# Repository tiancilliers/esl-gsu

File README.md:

This repository contains the design files for the satellite interfacing module in development by the ESL. More information will follow soon.

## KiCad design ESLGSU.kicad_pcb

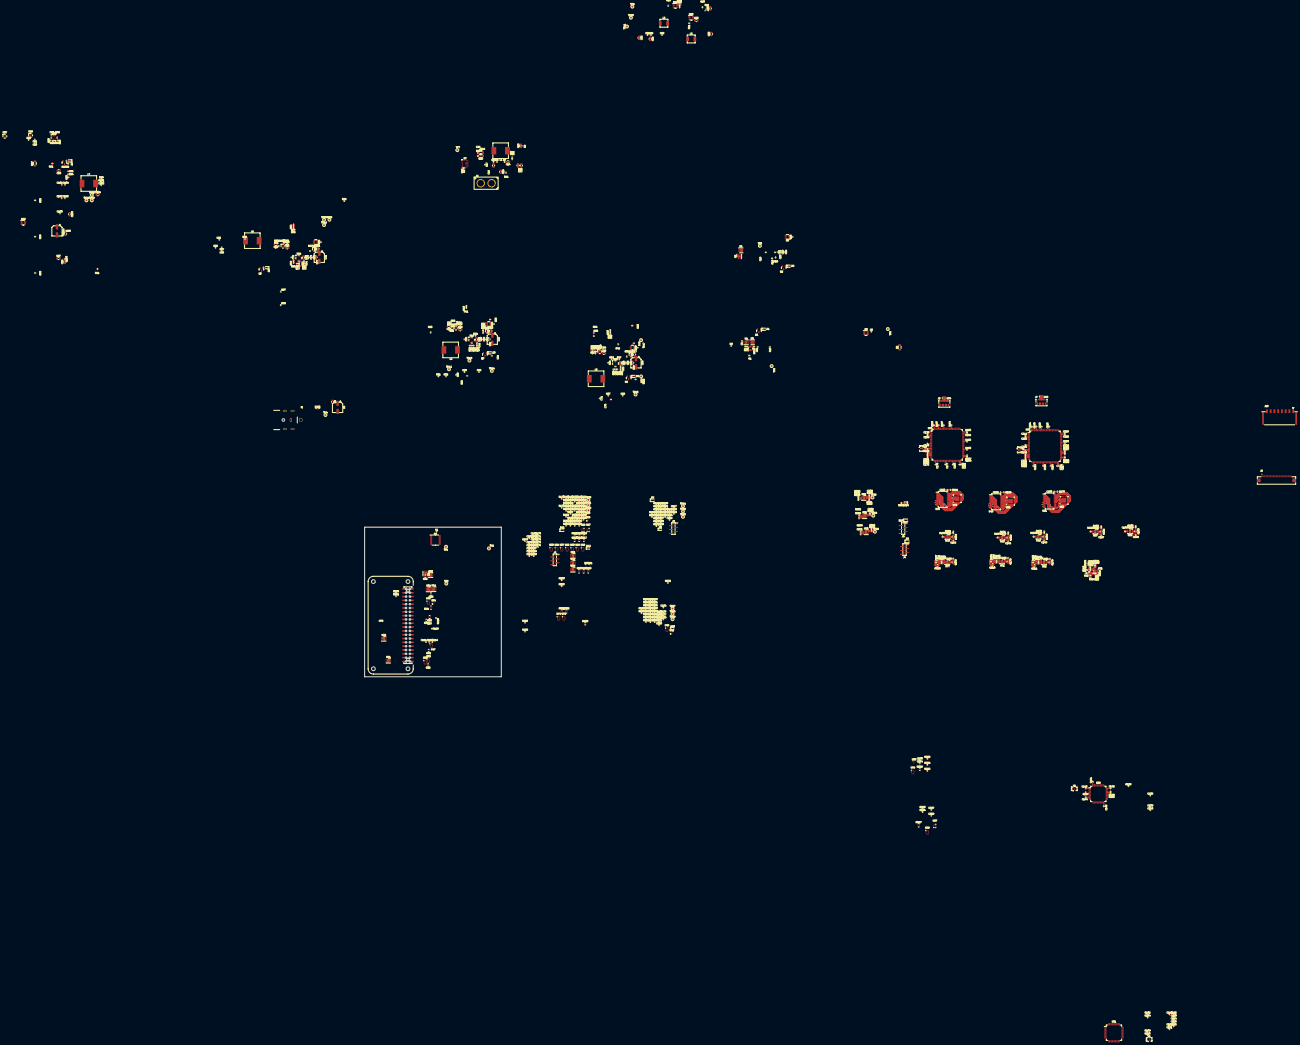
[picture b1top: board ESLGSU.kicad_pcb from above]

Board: 6 copper layers, 698 parts (0 on the bottom side), 467 nets.

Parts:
C1, C3, C5, C11, C12, C13, C17, C21, C25, C27, C31, C32, C36, C37, C38, C39, C48, C54, C55, C56, C57, C66, C72, C73, C74, C75, C84, C90, C91, C92, C93, C102, C108, C109, C110, C111, C112, C113, C114, C117, C118, C119, C122, C123, C124, C125, C126, C127, C128, C129, C130, C131, C132, C133, C136, C137, C138, C141, C142, C143, C144, C145, C146, C147, C148, C149, C150, C151, C152, C153, C154, C155, C156, C157, C158, C161, C162, C163, C164, C165, C166, C167, C168, C169, C170, C171, C172, C173, C174, C176, C177, C180, C181, C182, C183, C184, C187, C188, C189, C190, C191, C192, C193, C194, C195, C196, C197, C198, C199, C200, C201, C203, C204, C205, C206, C207, C208, C209, C210, C212, C213, C216, C217, C218, C219, C220, C223, C224, C225, C226, C227, C228, C229, C230: 100n; C_0402_1005Metric
C2, C16, C49, C52, C53, C67, C70, C71, C85, C88, C89, C103, C106, C107, C121, C140, C175, C179, C211, C215: 1u; C_0402_1005Metric
C4, C20, C42, C60, C78, C96: 22n; C_0402_1005Metric
C6, C7, C8, C18, C19, C30, C35: 10u; C_0805_2012Metric
C9, C40, C58, C76, C94: 100u; CP_Elec_6.3x7.7
C10, C24: 1n; C_0402_1005Metric
C14, C15, C22, C23, C28, C29, C33, C34, C41, C43, C44, C45, C46, C47, C59, C61, C62, C63, C64, C65, C77, C79, C80, C81, C82, C83, C95, C97, C98, C99, C100, C101: 22u; C_0805_2012Metric
C26, C120, C139, C178, C214: 4.7u; C_0402_1005Metric
C50, C68, C86, C104: 220p; C_0402_1005Metric
C51, C69, C87, C105: 2.2n; C_0402_1005Metric
C115, C134, C159, C160, C202: 100p; C_0402_1005Metric
C116, C135, C185, C186, C221, C222: 2.2u; C_0402_1005Metric
D1, D2, D3, D4, D5, D6, D8, D10, D12, D14: TZ-P2-0603GTCS1-0.6T; LED_0603_1608Metric
D7, D9, D11, D13: 1N5819; D_SOD-323
J1: PJ-080BH; PJ-082BH
J2: XT60U-M; XT60
J3, J4, J6, J8: Conn_01x06_Pin; PinHeader_1x06_P1.27mm_Vertical_SMD_Pin1Right
J5, J7: 10118194-0001LF; AMPHENOL_10118194-0001LF
J9: AMPHENOL_62684-401100ALF
J10: 1054301108; MOLEX_1054301108
L1, L4, L5, L6, L7: SRP1038A-4R7M; L_Vishay_IHLP-4040
L2, L3: SPM5020T-4R7M-LR; L_Vishay_IHLP-2020
Q1, Q2, Q3, Q4, Q5, Q6: RE1C002UNTCL; SOT-23
R1, R13: 200R; R_0402_1005Metric
R2, R14, R15, R16, R17, R119, R120, R122, R123, R152, R153, R155, R156, R176, R177, R190, R191, R192, R193, R194, R195, R196, R197, R230, R231, R237, R245, R246, R247, R248, R267, R268: 10K; R_0402_1005Metric
R3, R18: 20K; R_0402_1005Metric
R4, R9, R10, R31, R49, R72, R87: 5m; R_1206_3216Metric
R5, R6, R24, R25, R42, R43, R66, R67, R81, R82, R104, R109, R110, R111, R113, R121, R125, R133, R134, R137, R142, R143, R144, R146, R154, R158, R166, R167, R198, R204, R207, R213, R214, R222, R224, R227, R229, R249, R253, R255, R260, R261, R265, R270: 0R; R_0402_1005Metric
R7, R8, R11, R12: 1R; R_0402_1005Metric
R19, R21, R47, R105, R114, R127, R138, R147, R160, R170, R171, R172, R182, R184, R202, R203, R217, R218, R233, R234, R240, R252, R263: 100K; R_0402_1005Metric
R20, R22: 5.6K; R_0402_1005Metric
R23, R36, R54, R76, R91: 27K; R_0402_1005Metric
R26, R44, R68, R83: 47K; R_0402_1005Metric
R27, R45, R69, R84, R130, R163, R201, R251: 33R; R_0402_1005Metric
R28, R33, R46, R51, R52, R70, R74, R85, R89, R102, R106, R107, R108, R115, R116, R117, R118, R126, R128, R129, R131, R135, R139, R140, R141, R148, R149, R150, R151, R159, R161, R162, R164, R173, R174, R175, R180, R181, R183, R185, R186, R187, R188, R189, R199, R200, R205, R206, R208, R209, R210, R211, R215, R216, R219, R220, R221, R225, R226, R235, R236, R239, R241, R242, R243, R244, R250, R254, R256, R257, R258, R262, R264, R269, R272, R273: 200K; R_0402_1005Metric
R29, R37, R55, R56, R77, R92: 15K; R_0402_1005Metric
R30, R40, R58, R79, R94: 22K; R_0402_1005Metric
R32, R50, R73, R88: 8.2K; R_0402_1005Metric
R34: 330K; R_0402_1005Metric
R35: 1.5K; R_0402_1005Metric
R38: 12K; R_0402_1005Metric
R39, R71, R86: 150K; R_0402_1005Metric
R41, R59, R80, R95: 1K; R_0402_1005Metric
R48, R78, R93: 51K; R_0402_1005Metric
R53: 2.2K; R_0402_1005Metric
R57: 75K; R_0402_1005Metric
R60, R61, R62, R63, R64, R65, R96, R97, R98, R99, R100, R101: 4.7K; R_0402_1005Metric
R75, R90: 220K; R_0402_1005Metric
R103, R136, R168, R169, R178, R179, R232, R238: 120R; R_0805_2012Metric
R112, R124, R132, R145, R157, R165, R212, R223, R228, R259, R266, R271: 510R; R_0402_1005Metric
RN1, RN2, RN5, RN10, RN11, RN12, RN14, RN16, RN17, RN20, RN23, RN24, RN26: 0R; R_Array_Convex_2x0402
RN3, RN6, RN13, RN15, RN25: 10K; R_Array_Convex_2x0402
RN4, RN7, RN8, RN9, RN18, RN19, RN21, RN22, RN27: 0R; R_Array_Concave_4x0402
TP1, TP2, TP3, TP4, TP5, TP6, TP7, TP8, TP9, TP10, TP11, TP12, TP13, TP14, TP15, TP16, TP17, TP18, TP19, TP20, TP21, TP22, TP23, TP24, TP25, TP26, TP27, TP28, TP29, TP30, TP31, TP32, TP33, TP34, TP35: TestPoint; TestPoint_Pad_D1.5mm
U1: TCA9544APWR; TSSOP-20_4.4x6.5mm_P0.65mm
U2, U6: VBQF1303; V-DFN3030-8
U3, U13, U17, U21, U25: INA219AIDCNR; SOT-23-8
U4, U8: NCP45770IMN24TWG; WDFN-12-1EP_3x3mm_P0.45mm_EP1.7x2.5mm
U5, U9: AP74700QW6-7; SOT-23-6
U7: MP2651GVT; TQFN30_MP2651
U10: AP63205WU-7; TSOT-23-6
U11: TPS2121RUXR; Texas_VQFN-HR-12_2x2.5mm_P0.5mm_ThermalVias
U12: AP63203WU-7; TSOT-23-6
U14, U18, U22, U26: LM73100RPWR; VQFN-HR
U15, U19, U23, U27: TPS259474LRPWR; VQFN-HR
U16, U20, U24, U28: MP28167-A; QFN-16-MP28167
U29, U37, U45, U46, U73: TCAN1051GVDRBRQ; DFN-8-1EP_3x3mm_P0.65mm_EP1.55x2.4mm
U30, U33, U36, U38, U41, U44, U65, U70, U71, U86, U89, U90: TPS2115ADRBR; VSON-8-1EP_3x3mm_P0.65mm_EP1.65x2.4mm_ThermalVias
U31, U39: STM32F412RETx; LQFP-64_10x10mm_P0.5mm
U32, U35, U40, U43, U47, U53, U56, U57, U62, U63, U68, U69, U74, U78, U81, U84, U88: TMUX1574RSVR; T-UQFN-16
U34, U42, U58, U59, U82: FXMA2102L8X; UQFN8_MICROPAK
U48, U75, U91: CY8C9520A; SSOP-28_5.3x10.2mm_P0.65mm
U49, U50, U60, U61, U76, U83: TXU0202DTTR; SOT833-1-XSON8
U51, U52, U77: THVD1450DRBR; DFN-8-1EP_3x3mm_P0.65mm_EP1.55x2.4mm
U54, U80: ESD7004MUTAG; UDFN10_ESD
U55, U79, U92: PCAL6524HEAZ; HVQFN-32-1EP_5x5mm_P0.5mm_EP3.1x3.1mm
U64, U85: STM32H743ZITx; LQFP-144_20x20mm_P0.5mm
U66, U67, U87: TXB0104RUT; T-UQFN-12
U72: FH-00339; PI_ZERO_2_W
Y1, Y2, Y3, Y4: CSTNE8M00G55A; Resonator_SMD_Murata_CSTxExxV-3Pin_3.0x1.1mm

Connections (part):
/BUS_3V3: C110.2, C129.2, C169.2, J10.1, R31.2, R113.2, R146.2, R224.2, TP14.1, U13.2 (IN-), U30.8 (IN1), U38.8 (IN1), U70.8 (IN1)
/BUS_5V: C112.2, C131.2, C173.2, J10.2, R49.1, R125.2, R158.2, R229.2, TP17.1, U17.2 (IN-), U33.8 (IN1), U41.8 (IN1), U71.8 (IN1)
/BUS_CH1: J10.7, R72.1, TP20.1, U21.2 (IN-)
/BUS_CH2: J10.8, R87.1, TP23.1, U25.2 (IN-)
/BUS_UNREG: C49.1, C67.1, C85.1, C103.1, J10.4, J10.5, R4.2, R28.1, R46.1, R70.1, R85.1, TP6.1, U3.2 (IN-), U15.5 (IN), U19.5 (IN), U23.5 (IN), U27.5 (IN)
/CAN1_H: J9.03 (Pin_3), R103.1, R136.1, R168.1, R232.1, U29.7 (CANH), U37.7 (CANH), U45.7 (CANH), U73.7 (CANH)
/CAN1_L: J9.02 (Pin_2), R103.2, R136.2, R168.2, R232.2, U29.6 (CANL), U37.6 (CANL), U45.6 (CANL), U73.6 (CANL)
/CAN2_H: J9.05 (Pin_5), R169.1, U46.7 (CANH)
/CAN2_L: J9.04 (Pin_4), R169.2, U46.6 (CANL)
/CFGI2C_SCL: R231.2, RN20.1 (R1.1), U48.10 (SCL), U55.26 (ADDR), U55.29 (SCL), U72.5 (GPIO3_SCL), U75.10 (SCL), U79.29 (SCL), U91.10 (SCL), U92.29 (SCL)
/CFGI2C_SDA: R230.2, RN20.2 (R2.1), U48.11 (SDA), U55.30 (SDA), U72.3 (GPIO2_SDA), U75.11 (SDA), U79.26 (ADDR), U79.30 (SDA), U91.11 (SDA), U92.30 (SDA)
/EPS_I2C_INT: TP3.1, U1.17 (~INT), U85.80 (PD11)
/EPS_I2C_SCL: R267.2, RN20.4 (R1.2), TP1.1, U1.18 (SCL), U3.5 (SCL), U7.4 (SCL), U85.81 (PD12)
/EPS_I2C_SDA: R268.2, RN20.3 (R2.2), TP2.1, U1.19 (SDA), U3.6 (SDA), U7.3 (SDA), U85.82 (PD13)
/EPS_uC/BOOTLDR: R243.2, U72.40 (GPIO21), U85.138 (BOOT0)
/EPS_uC/CAN1_RX: U73.4 (RXD), U85.139 (PB8)
/EPS_uC/CAN1_SE: R234.1, R236.2, U73.8 (S), U75.1 (P0_0), U79.1 (P0_0)
/EPS_uC/CAN1_TX: U73.1 (TXD), U85.140 (PB9)
/EPS_uC/GPIO_nEN: R233.1, R235.2, U74.13 (nEN), U75.12 (P2_3_A1), U78.13 (nEN), U79.20 (P2_3)
/EPS_uC/I2C1_EN: R250.1, U75.3 (P0_2), U79.3 (P0_2), U82.5 (OE)
/EPS_uC/I2C1_nPEN: R240.1, R241.1, U75.4 (P0_3), U79.4 (P0_3), U81.13 (nEN)
/EPS_uC/LED: R251.1, U85.34 (PA0)
/EPS_uC/PISPI_NSS: U72.35 (GPIO19), U85.40 (PA4)
/EPS_uC/RS4851_EN: R237.2, R239.1, U75.2 (P0_1), U77.2 (nRE), U77.3 (DE), U79.2 (P0_1)
/EPS_uC/RS4851_RX: RN23.4 (R1.2), U76.4 (A2Y), U85.114 (PD0)
/EPS_uC/RS4851_TX: RN23.3 (R2.2), U76.5 (A1), U85.115 (PD1)
/EPS_uC/RS4851_TXE: R237.1, U85.118 (PD4)
/EPS_uC/SPI1_nEN: R263.1, R264.2, U75.7 (P0_6), U79.7 (P0_6), U88.13 (nEN)
/EPS_uC/SPI_SHIFT: U75.8 (P0_7), U79.8 (P0_7), U87.12 (OE), U88.15 (SEL)
/EPS_uC/SUB3V3: C194.2, C197.2, C203.2, C209.2, C211.1, C212.1, C213.1, C214.1, C215.1, C216.1, C217.1, C218.1, C219.1, C220.1, C223.1, C224.1, C225.1, C226.1, C227.1, C228.1, C229.1, D13.1 (K), R245.1, R246.1, R265.1, R267.1, R268.1, TP34.1, U73.5 (VIO), U76.3 (VCCA), U76.6 (OE), U82.1 (VREF1), U83.3 (VCCA), U83.6 (OE), U85.6 (VBAT), U85.17 (VDD), U85.30 (VDD), U85.32 (VREF+), U85.33 (VDDA), U85.39 (VDD), U85.52 (VDD), U85.62 (VDD), U85.72 (VDD), U85.84 (VDD), U85.95 (VDD33_USB), U85.108 (VDD), U85.121 (VDD), U85.131 (VDD), U85.144 (VDD), U87.1 (VCCA), U89.7 (OUT)
/EPS_uC/SUB5V: C195.2, R234.2, R270.1, TP35.1, U73.3 (VCC), U90.7 (OUT)
/EPS_uC/SWCLK: J8.4, U85.109 (PA14)
/EPS_uC/SWDIO: J8.3, U85.105 (PA13)
/EPS_uC/SWO: J8.5, U85.133 (PB3)
/EPS_uC/UART1_REV: R256.2, U75.6 (P0_5), U79.6 (P0_5), U84.15 (SEL)
/EPS_uC/UART1_nEN: R252.1, R254.2, U75.5 (P0_4), U79.5 (P0_4), U84.13 (nEN)
/EPS_uC/USB_D+: J7.3 (D+), U80.4 (IO3), U80.7 (NC3), U85.104 (PA12)
/EPS_uC/USB_D-: J7.2 (D-), U80.2 (IO2), U80.9 (NC2), U85.103 (PA11)
/EPS_uC/USB_ID: J7.4 (ID), U80.5 (IO4), U80.6 (NC4), U85.102 (PA10)
/EPS_uC/USB_VBUS: J7.1 (VBUS), U80.1 (IO1), U80.10 (NC1), U85.101 (PA9)
/EPS_uC/VBUS: C196.2, C198.2, C199.2, C201.1, C204.2, C207.2, R233.2, R240.2, R242.1, R252.2, R260.1, R261.1, R263.2, RN25.1 (R1.1), RN25.2 (R2.1), TP33.1, U74.14 (VDD), U76.7 (VCCB), U77.8 (VCC), U78.14 (VDD), U81.2 (D1), U81.5 (D2), U81.14 (VDD), U83.7 (VCCB), U84.14 (VDD), U86.7 (OUT), U87.11 (VCCB), U88.14 (VDD)
/EPS_uC/_GPIO_1: RN21.5 (R4.2), U74.16 (S1A), U85.12 (PF2)
/EPS_uC/_GPIO_2: RN21.6 (R3.2), U74.3 (S2A), U85.13 (PF3)
/EPS_uC/_GPIO_3: RN21.7 (R2.2), U74.9 (S3A), U85.14 (PF4)
/EPS_uC/_GPIO_4: RN21.8 (R1.2), U74.12 (S4A), U85.15 (PF5)
/EPS_uC/_GPIO_5: RN22.5 (R4.2), U78.16 (S1A), U85.18 (PF6)
/EPS_uC/_GPIO_6: RN22.6 (R3.2), U78.3 (S2A), U85.19 (PF7)
/EPS_uC/_GPIO_7: RN22.7 (R2.2), U78.9 (S3A), U85.20 (PF8)
/EPS_uC/_GPIO_8: RN22.8 (R1.2), U78.12 (S4A), U85.21 (PF9)
/EPS_uC/_I2C1_SCL: R245.2, RN24.3 (R2.2), U82.2 (SCL1), U85.136 (PB6)
/EPS_uC/_I2C1_SDA: R246.2, RN24.4 (R1.2), U82.3 (SDA1), U85.137 (PB7)
/EPS_uC/_SPI1_MISO: RN27.8 (R1.2), U85.112 (PC11), U87.5 (A4), U88.12 (S4A)
/EPS_uC/_SPI1_MOSI: RN27.5 (R4.2), U85.113 (PC12), U87.2 (A1), U88.16 (S1A)
/EPS_uC/_SPI1_NSS: RN27.7 (R2.2), U85.110 (PA15), U87.4 (A3), U88.9 (S3A)
/EPS_uC/_SPI1_SCK: RN27.6 (R3.2), U85.111 (PC10), U87.3 (A2), U88.3 (S2A)
/EPS_uC/_UART1_RX: RN26.4 (R1.2), U83.4 (A2Y), U85.37 (PA3)
/EPS_uC/_UART1_TX: RN26.3 (R2.2), U83.5 (A1), U85.36 (PA2)
/EPS_uC/nRST: J8.2, U72.38 (GPIO20), U85.25 (NRST)
/EPS_uC/nVSYS: R262.2, R269.2, U75.15 (P2_2_WD), U79.19 (P2_2), U89.2 (D0), U90.2 (D0)
/EPS_uC/nVT3V3: R258.2, U75.18 (P2_0_A3), U79.17 (P2_0), U86.2 (D0)
/EPS_uC/nVT5V: R257.2, U75.17 (P2_1_A2), U79.18 (P2_1), U86.3 (D1)
/Fixed_Regulators/INT_3V3: R60.2, U1.7 (~INT1), U16.4 (ALT)
/Fixed_Regulators/INT_5V: R63.2, U1.4 (~INT0), U20.4 (ALT)
/Fixed_Regulators/SCL_3V3: R61.2, U1.9 (SC1), U13.5 (SCL), U16.5 (SCL)
/Fixed_Regulators/SCL_5V: R64.2, U1.6 (SC0), U17.5 (SCL), U20.5 (SCL)
/Fixed_Regulators/SDA_3V3: R62.2, U1.8 (SD1), U13.6 (SDA), U16.6 (SDA)
/Fixed_Regulators/SDA_5V: R65.2, U1.5 (SD0), U17.6 (SDA), U20.6 (SDA)
/GPIO_1: J9.32, RN7.4 (R4.1), RN8.4 (R4.1), RN21.4 (R4.1), U43.2 (D1), U47.2 (D1), U74.2 (D1)
/GPIO_2: J9.33, RN7.3 (R3.1), RN8.3 (R3.1), RN21.3 (R3.1), U43.5 (D2), U47.5 (D2), U74.5 (D2)
/GPIO_3: J9.34, RN7.2 (R2.1), RN8.2 (R2.1), RN21.2 (R2.1), U43.7 (D3), U47.7 (D3), U74.7 (D3)
/GPIO_4: J9.35, RN7.1 (R1.1), RN8.1 (R1.1), RN21.1 (R1.1), U43.10 (D4), U47.10 (D4), U74.10 (D4)
/GPIO_5: J9.36, RN4.4 (R4.1), RN9.4 (R4.1), RN22.4 (R4.1), U35.2 (D1), U53.2 (D1), U78.2 (D1)
/GPIO_6: J9.37, RN4.3 (R3.1), RN9.3 (R3.1), RN22.3 (R3.1), U35.5 (D2), U53.5 (D2), U78.5 (D2)
/GPIO_7: J9.38, RN4.2 (R2.1), RN9.2 (R2.1), RN22.2 (R2.1), U35.7 (D3), U53.7 (D3), U78.7 (D3)
/GPIO_8: J9.39, RN4.1 (R1.1), RN9.1 (R1.1), RN22.1 (R1.1), U35.10 (D4), U53.10 (D4), U78.10 (D4)
/I2C1_SCL: J9.17, R122.2, R155.2, R194.2, R247.2, RN2.2 (R2.1), RN3.3 (R2.2), RN5.2 (R2.1), RN6.3 (R2.2), RN12.2 (R2.1), RN13.3 (R2.2), RN24.2 (R2.1), RN25.3 (R2.2), U34.7 (SCL2), U42.7 (SCL2), U58.7 (SCL2), U82.7 (SCL2)
/I2C1_SDA: J9.18, R123.2, R156.2, R195.2, R248.2, RN2.1 (R1.1), RN3.4 (R1.2), RN5.1 (R1.1), RN6.4 (R1.2), RN12.1 (R1.1), RN13.4 (R1.2), RN24.1 (R1.1), RN25.4 (R1.2), U34.6 (SDA2), U42.6 (SDA2), U58.6 (SDA2), U82.6 (SDA2)
/I2C2_SCL: J9.19, R196.2, RN14.2 (R2.1), RN15.3 (R2.2), U59.7 (SCL2)
/I2C2_SDA: J9.20, R197.2, RN14.1 (R1.1), RN15.4 (R1.2), U59.6 (SDA2)
/Main_uC/BOOTLDR: R187.2, U64.138 (BOOT0), U72.12 (GPIO18)
/Main_uC/CAN1_RX: U45.4 (RXD), U64.139 (PB8)
/Main_uC/CAN1_SE: R171.1, R174.2, U45.8 (S), U48.1 (P0_0), U55.1 (P0_0)
/Main_uC/CAN1_TX: U45.1 (TXD), U64.140 (PB9)
/Main_uC/CAN2_RX: U46.4 (RXD), U64.78 (PD9)
/Main_uC/CAN2_SE: R172.1, R175.2, U46.8 (S), U48.2 (P0_1), U55.2 (P0_1)
/Main_uC/CAN2_TX: U46.1 (TXD), U64.79 (PD10)
/Main_uC/GPIO_nEN: R170.1, R173.2, U47.13 (nEN), U48.20 (P1_7_A4), U53.13 (nEN), U55.16 (P1_7)
/Main_uC/I2C1_EN: R199.1, U48.5 (P0_4), U55.5 (P0_4), U58.5 (OE)
/Main_uC/I2C1_nPEN: R182.1, R183.1, U48.6 (P0_5), U55.6 (P0_5), U56.13 (nEN)
/Main_uC/I2C2_EN: R200.1, U48.7 (P0_6), U55.7 (P0_6), U59.5 (OE)
/Main_uC/I2C2_nPEN: R184.1, R185.1, U48.8 (P0_7), U55.8 (P0_7), U57.13 (nEN)
/Main_uC/LED: R201.1, U64.34 (PA0)
/Main_uC/PISPI_NSS: U64.40 (PA4), U72.36 (GPIO16)
/Main_uC/RS4851_EN: R176.2, R180.1, U48.3 (P0_2), U51.2 (nRE), U51.3 (DE), U55.3 (P0_2)
/Main_uC/RS4851_RX: RN10.4 (R1.2), U49.4 (A2Y), U64.114 (PD0)
/Main_uC/RS4851_TX: RN10.3 (R2.2), U49.5 (A1), U64.115 (PD1)
/Main_uC/RS4851_TXE: R176.1, U64.118 (PD4)
/Main_uC/RS4852_EN: R177.2, R181.1, U48.4 (P0_3), U52.2 (nRE), U52.3 (DE), U55.4 (P0_3)
/Main_uC/RS4852_RX: RN11.4 (R1.2), U50.4 (A2Y), U64.97 (PC7)
/Main_uC/RS4852_TX: RN11.3 (R2.2), U50.5 (A1), U64.96 (PC6)
/Main_uC/RS4852_TXE: R177.1, U64.119 (PD5)
/Main_uC/SPI1_nEN: R218.1, R220.2, U48.23 (P1_4), U55.13 (P1_4), U69.13 (nEN)
/Main_uC/SPI2_nEN: R217.1, R219.2, U48.22 (P1_5_A6), U55.14 (P1_5), U68.13 (nEN)
/Main_uC/SPI_SHIFT: R221.2, U48.21 (P1_6_A5), U55.15 (P1_6), U66.12 (OE), U67.12 (OE), U68.15 (SEL), U69.15 (SEL)
/Main_uC/SUB3V3: C146.2, C149.2, C151.2, C153.2, C161.2, C163.2, C171.2, C172.2, C175.1, C176.1, C177.1, C178.1, C179.1, C180.1, C181.1, C182.1, C183.1, C184.1, C187.1, C188.1, C189.1, C190.1, C191.1, C192.1, C193.1, D11.1 (K), R190.1, R191.1, R192.1, R193.1, R222.1, R224.1, TP31.1, U45.5 (VIO), U46.5 (VIO), U49.3 (VCCA), U49.6 (OE), U50.3 (VCCA), U50.6 (OE), U58.1 (VREF1), U59.1 (VREF1), U60.3 (VCCA), U60.6 (OE), U61.3 (VCCA), U61.6 (OE), U64.6 (VBAT), U64.17 (VDD), U64.30 (VDD), U64.32 (VREF+), U64.33 (VDDA), U64.39 (VDD), U64.52 (VDD), U64.62 (VDD), U64.72 (VDD), U64.84 (VDD), U64.95 (VDD33_USB), U64.108 (VDD), U64.121 (VDD), U64.131 (VDD), U64.144 (VDD), U66.1 (VCCA), U67.1 (VCCA), U70.7 (OUT)
/Main_uC/SUB5V: C147.2, C150.2, R171.2, R172.2, R227.1, R229.1, TP32.1, U45.3 (VCC), U46.3 (VCC), U71.7 (OUT)
/Main_uC/SWCLK: J6.4, U64.109 (PA14)
/Main_uC/SWDIO: J6.3, U64.105 (PA13)
/Main_uC/SWO: J6.5, U64.133 (PB3)
/Main_uC/UART1_REV: R209.2, U48.26 (P1_1), U55.10 (P1_1), U63.15 (SEL)
/Main_uC/UART1_nEN: R203.1, R206.2, U48.27 (P1_0), U55.9 (P1_0), U63.13 (nEN)
/Main_uC/UART2_REV: R208.2, U48.24 (P1_3), U55.12 (P1_3), U62.15 (SEL)
/Main_uC/UART2_nEN: R202.1, R205.2, U48.25 (P1_2), U55.11 (P1_2), U62.13 (nEN)
/Main_uC/USB_D+: J5.3 (D+), U54.4 (IO3), U54.7 (NC3), U64.104 (PA12)
/Main_uC/USB_D-: J5.2 (D-), U54.2 (IO2), U54.9 (NC2), U64.103 (PA11)
/Main_uC/USB_ID: J5.4 (ID), U54.5 (IO4), U54.6 (NC4), U64.102 (PA10)
/Main_uC/USB_VBUS: J5.1 (VBUS), U54.1 (IO1), U54.10 (NC1), U64.101 (PA9)
/Main_uC/VBUS: C148.2, C152.2, C154.2, C155.2, C157.1, C158.1, C162.2, C164.2, C167.2, C168.2, R170.2, R182.2, R184.2, R186.1, R188.1, R202.2, R203.2, R213.1, R214.1, R217.2, R218.2, RN13.1 (R1.1), RN13.2 (R2.1), RN15.1 (R1.1), RN15.2 (R2.1), TP30.1, U47.14 (VDD), U49.7 (VCCB), U50.7 (VCCB), U51.8 (VCC), U52.8 (VCC), U53.14 (VDD), U56.2 (D1), U56.5 (D2), U56.14 (VDD), U57.2 (D1), U57.5 (D2), U57.14 (VDD), U60.7 (VCCB), U61.7 (VCCB), U62.14 (VDD), U63.14 (VDD), U65.7 (OUT), U66.11 (VCCB), U67.11 (VCCB), U68.14 (VDD), U69.14 (VDD)
/Main_uC/_GPIO_1: RN8.5 (R4.2), U47.16 (S1A), U64.12 (PF2)
/Main_uC/_GPIO_2: RN8.6 (R3.2), U47.3 (S2A), U64.13 (PF3)
/Main_uC/_GPIO_3: RN8.7 (R2.2), U47.9 (S3A), U64.14 (PF4)
/Main_uC/_GPIO_4: RN8.8 (R1.2), U47.12 (S4A), U64.15 (PF5)
/Main_uC/_GPIO_5: RN9.5 (R4.2), U53.16 (S1A), U64.18 (PF6)
/Main_uC/_GPIO_6: RN9.6 (R3.2), U53.3 (S2A), U64.19 (PF7)
/Main_uC/_GPIO_7: RN9.7 (R2.2), U53.9 (S3A), U64.20 (PF8)
/Main_uC/_GPIO_8: RN9.8 (R1.2), U53.12 (S4A), U64.21 (PF9)
/Main_uC/_I2C1_SCL: R190.2, RN12.3 (R2.2), U58.2 (SCL1), U64.136 (PB6)
/Main_uC/_I2C1_SDA: R191.2, RN12.4 (R1.2), U58.3 (SDA1), U64.137 (PB7)
/Main_uC/_I2C2_SCL: R192.2, RN14.3 (R2.2), U59.2 (SCL1), U64.11 (PF1)
/Main_uC/_I2C2_SDA: R193.2, RN14.4 (R1.2), U59.3 (SDA1), U64.10 (PF0)
/Main_uC/_SPI1_MISO: RN19.8 (R1.2), U64.112 (PC11), U67.5 (A4), U69.12 (S4A)
/Main_uC/_SPI1_MOSI: RN19.5 (R4.2), U64.113 (PC12), U67.2 (A1), U69.16 (S1A)
/Main_uC/_SPI1_NSS: RN19.7 (R2.2), U64.110 (PA15), U67.4 (A3), U69.9 (S3A)
/Main_uC/_SPI1_SCK: RN19.6 (R3.2), U64.111 (PC10), U67.3 (A2), U69.3 (S2A)
/Main_uC/_SPI2_MISO: RN18.8 (R1.2), U64.66 (PE13), U66.5 (A4), U68.12 (S4A)
/Main_uC/_SPI2_MOSI: RN18.5 (R4.2), U64.67 (PE14), U66.2 (A1), U68.16 (S1A)
/Main_uC/_SPI2_NSS: RN18.7 (R2.2), U64.64 (PE11), U66.4 (A3), U68.9 (S3A)
/Main_uC/_SPI2_SCK: RN18.6 (R3.2), U64.65 (PE12), U66.3 (A2), U68.3 (S2A)
/Main_uC/_UART1_RX: RN17.4 (R1.2), U61.4 (A2Y), U64.37 (PA3)
/Main_uC/_UART1_TX: RN17.3 (R2.2), U61.5 (A1), U64.36 (PA2)
/Main_uC/_UART2_RX: RN16.4 (R1.2), U60.4 (A2Y), U64.70 (PB11)
/Main_uC/_UART2_TX: RN16.3 (R2.2), U60.5 (A1), U64.69 (PB10)
/Main_uC/nRST: J6.2, U64.25 (NRST), U72.11 (GPIO17)
/Main_uC/nVBUS: R216.2, R226.2, U48.12 (P2_3_A1), U55.20 (P2_3), U70.2 (D0), U71.2 (D0)
/Main_uC/nVSYS: R215.2, R225.2, U48.15 (P2_2_WD), U55.19 (P2_2), U70.3 (D1), U71.3 (D1)
/Main_uC/nVT3V3: R211.2, U48.18 (P2_0_A3), U55.17 (P2_0), U65.2 (D0)
/Main_uC/nVT5V: R210.2, U48.17 (P2_1_A2), U55.18 (P2_1), U65.3 (D1)
/Misc_uC_Combined/Misc_uCs1/CAN1_RX: U29.4 (RXD), U31.57 (PB5)
/Misc_uC_Combined/Misc_uCs1/CAN1_TX: U29.1 (TXD), U31.34 (PB13)
/Misc_uC_Combined/Misc_uCs1/LED: R130.1, U31.14 (PA0)
/Misc_uC_Combined/Misc_uCs1/SUB3V3: C108.2, C120.1, C121.1, C122.1, C123.1, C124.1, C125.1, C126.1, D7.1 (K), R111.1, R113.1, R119.1, R120.1, TP24.1, U29.5 (VIO), U30.7 (OUT), U31.1 (VBAT), U31.13 (VDDA), U31.19 (VDD), U31.32 (VDD), U31.48 (VDD), U31.64 (VDD), U34.1 (VREF1)
/Misc_uC_Combined/Misc_uCs1/SUB5V: C109.2, R105.2, R121.1, R125.1, TP25.1, U29.3 (VCC), U33.7 (OUT)
/Misc_uC_Combined/Misc_uCs1/SWCLK: J3.4, U31.49 (PA14)
/Misc_uC_Combined/Misc_uCs1/SWDIO: J3.3, U31.46 (PA13)
/Misc_uC_Combined/Misc_uCs1/SWO: J3.5, U31.55 (PB3)
/Misc_uC_Combined/Misc_uCs1/VBUS: C114.1, C117.2, R114.2, R118.1, R127.2, R133.1, R134.1, RN3.1 (R1.1), RN3.2 (R2.1), TP26.1, U32.2 (D1), U32.5 (D2), U32.14 (VDD), U35.14 (VDD), U36.7 (OUT)
/Misc_uC_Combined/Misc_uCs1/_GPIO_1: RN4.5 (R4.2), U31.8 (PC0), U35.16 (S1A)
/Misc_uC_Combined/Misc_uCs1/_GPIO_2: RN4.6 (R3.2), U31.9 (PC1), U35.3 (S2A)
/Misc_uC_Combined/Misc_uCs1/_GPIO_3: RN4.7 (R2.2), U31.10 (PC2), U35.9 (S3A)
/Misc_uC_Combined/Misc_uCs1/_GPIO_4: RN4.8 (R1.2), U31.11 (PC3), U35.12 (S4A)
/Misc_uC_Combined/Misc_uCs1/_I2C1_SCL: R119.2, RN2.3 (R2.2), U31.58 (PB6), U34.2 (SCL1)
/Misc_uC_Combined/Misc_uCs1/_I2C1_SDA: R120.2, RN2.4 (R1.2), U31.59 (PB7), U34.3 (SDA1)
/Misc_uC_Combined/Misc_uCs/CAN1_RX: U37.4 (RXD), U39.57 (PB5)
/Misc_uC_Combined/Misc_uCs/CAN1_TX: U37.1 (TXD), U39.34 (PB13)
/Misc_uC_Combined/Misc_uCs/LED: R163.1, U39.14 (PA0)
/Misc_uC_Combined/Misc_uCs/SUB3V3: C127.2, C139.1, C140.1, C141.1, C142.1, C143.1, C144.1, C145.1, D9.1 (K), R144.1, R146.1, R152.1, R153.1, TP27.1, U37.5 (VIO), U38.7 (OUT), U39.1 (VBAT), U39.13 (VDDA), U39.19 (VDD), U39.32 (VDD), U39.48 (VDD), U39.64 (VDD), U42.1 (VREF1)
/Misc_uC_Combined/Misc_uCs/SUB5V: C128.2, R138.2, R154.1, R158.1, TP28.1, U37.3 (VCC), U41.7 (OUT)
/Misc_uC_Combined/Misc_uCs/SWCLK: J4.4, U39.49 (PA14)
/Misc_uC_Combined/Misc_uCs/SWDIO: J4.3, U39.46 (PA13)
/Misc_uC_Combined/Misc_uCs/SWO: J4.5, U39.55 (PB3)
/Misc_uC_Combined/Misc_uCs/VBUS: C133.1, C136.2, R147.2, R151.1, R160.2, R166.1, R167.1, RN6.1 (R1.1), RN6.2 (R2.1), TP29.1, U40.2 (D1), U40.5 (D2), U40.14 (VDD), U43.14 (VDD), U44.7 (OUT)
/Misc_uC_Combined/Misc_uCs/_GPIO_1: RN7.5 (R4.2), U39.8 (PC0), U43.16 (S1A)
/Misc_uC_Combined/Misc_uCs/_GPIO_2: RN7.6 (R3.2), U39.9 (PC1), U43.3 (S2A)
/Misc_uC_Combined/Misc_uCs/_GPIO_3: RN7.7 (R2.2), U39.10 (PC2), U43.9 (S3A)
/Misc_uC_Combined/Misc_uCs/_GPIO_4: RN7.8 (R1.2), U39.11 (PC3), U43.12 (S4A)
/Misc_uC_Combined/Misc_uCs/_I2C1_SCL: R152.2, RN5.3 (R2.2), U39.58 (PB6), U42.2 (SCL1)
/Misc_uC_Combined/Misc_uCs/_I2C1_SDA: R153.2, RN5.4 (R1.2), U39.59 (PB7), U42.3 (SDA1)
/Misc_uC_Combined/PI_BOOTLDR_MISC1: R135.2, U39.60 (BOOT0), U72.18 (GPIO24)
/Misc_uC_Combined/PI_BOOTLDR_MISC2: R102.2, U31.60 (BOOT0), U72.13 (GPIO27)
/Misc_uC_Combined/PI_SS_MISC1: U39.50 (PA15), U72.15 (GPIO22)
/Misc_uC_Combined/PI_SS_MISC2: U31.50 (PA15), U72.22 (GPIO25)
/Misc_uC_Combined/PI_nRST_MISC1: J4.2, U39.7 (NRST), U72.16 (GPIO23)
/Misc_uC_Combined/PI_nRST_MISC2: J3.2, U31.7 (NRST), U72.37 (GPIO26)
/Misc_uC_Combined/UC1_CANSE: R138.1, R141.2, U37.8 (S), U91.1 (P0_0), U92.1 (P0_0)
/Misc_uC_Combined/UC1_GPIONEN: R160.1, R164.2, U43.13 (nEN), U91.4 (P0_3), U92.4 (P0_3)
/Misc_uC_Combined/UC1_I2CEN: R159.1, U42.5 (OE), U91.3 (P0_2), U92.3 (P0_2)
/Misc_uC_Combined/UC1_I2CNPEN: R147.1, R148.1, U40.13 (nEN), U91.2 (P0_1), U92.2 (P0_1)
/Misc_uC_Combined/UC1_NVBUS: R140.2, R150.2, U38.2 (D0), U41.2 (D0), U91.7 (P0_6), U92.7 (P0_6)
/Misc_uC_Combined/UC1_NVSYS: R139.2, R149.2, U38.3 (D1), U41.3 (D1), U91.8 (P0_7), U92.8 (P0_7)
/Misc_uC_Combined/UC1_NVT3V3: R162.2, U44.2 (D0), U91.5 (P0_4), U92.5 (P0_4)
/Misc_uC_Combined/UC1_NVT5V: R161.2, U44.3 (D1), U91.6 (P0_5), U92.6 (P0_5)
/Misc_uC_Combined/UC2_CANSE: R105.1, R108.2, U29.8 (S), U91.27 (P1_0), U92.9 (P1_0)
/Misc_uC_Combined/UC2_GPIONEN: R127.1, R131.2, U35.13 (nEN), U91.24 (P1_3), U92.12 (P1_3)
/Misc_uC_Combined/UC2_I2CEN: R126.1, U34.5 (OE), U91.25 (P1_2), U92.11 (P1_2)
/Misc_uC_Combined/UC2_I2CNPEN: R114.1, R115.1, U32.13 (nEN), U91.26 (P1_1), U92.10 (P1_1)
/Misc_uC_Combined/UC2_NVBUS: R107.2, R117.2, U30.2 (D0), U33.2 (D0), U91.21 (P1_6_A5), U92.15 (P1_6)
/Misc_uC_Combined/UC2_NVSYS: R106.2, R116.2, U30.3 (D1), U33.3 (D1), U91.20 (P1_7_A4), U92.16 (P1_7)
/Misc_uC_Combined/UC2_NVT3V3: R129.2, U36.2 (D0), U91.23 (P1_4), U92.13 (P1_4)
/Misc_uC_Combined/UC2_NVT5V: R128.2, U36.3 (D1), U91.22 (P1_5_A6), U92.14 (P1_5)
/PISER_RX: R109.1, R142.1, R204.1, R253.1, RN1.4 (R1.2), U72.10 (GPIO15_RX)
/PISER_TX: R110.1, R143.1, R207.1, R255.1, RN1.3 (R2.2), U72.8 (GPIO14_TX)
/PISPI_MISO: U31.52 (PC11), U39.52 (PC11), U64.42 (PA6), U72.21 (GPIO9_MISO), U85.42 (PA6)
/PISPI_MOSI: U31.53 (PC12), U39.53 (PC12), U64.43 (PA7), U72.19 (GPIO10_MOSI), U85.43 (PA7)
/PISPI_SCK: U31.51 (PC10), U39.51 (PC10), U64.41 (PA5), U72.23 (GPIO11_SCLK), U85.41 (PA5)
/Programmable_Regulators/INT_CH1: R96.2, U1.11 (~INT2), U24.4 (ALT)
/Programmable_Regulators/INT_CH2: R99.2, U1.14 (~INT3), U28.4 (ALT)
/Programmable_Regulators/SCL_CH1: R97.2, U1.13 (SC2), U21.5 (SCL), U24.5 (SCL)
/Programmable_Regulators/SCL_CH2: R100.2, U1.16 (SC3), U25.5 (SCL), U28.5 (SCL)
/Programmable_Regulators/SDA_CH1: R98.2, U1.12 (SD2), U21.6 (SDA), U24.6 (SDA)
/Programmable_Regulators/SDA_CH2: R101.2, U1.15 (SD3), U25.6 (SDA), U28.6 (SDA)
/RAW_BAT_BUS: U8.11 (EN), U75.22 (P1_5_A6), U79.14 (P1_5)
/RAW_PIN_BUS: U4.11 (EN), U75.23 (P1_4), U79.13 (P1_4)
/REG_3V3_EF: R32.1, R36.1, U75.27 (P1_0), U79.9 (P1_0)
/REG_3V3_EN: U16.3 (EN), U85.87 (PG2)
/REG_5V_EF: R50.1, R54.1, U75.26 (P1_1), U79.10 (P1_1)
/REG_5V_EN: U20.3 (EN), U85.88 (PG3)
/REG_CH1_EF: R73.1, R76.1, U75.25 (P1_2), U79.11 (P1_2)
/REG_CH1_EN: U22.1 (EN/UVLO), U22.4 (PGTH), U24.3 (EN), U26.1 (EN/UVLO), U26.4 (PGTH), U85.89 (PG4)
/REG_CH2_EF: R88.1, R91.1, U75.24 (P1_3), U79.12 (P1_3)
/REG_CH2_EN: U28.3 (EN), U85.90 (PG5)
/RS4851_A: J9.07 (Pin_7), R178.2, R238.2, U51.6 (A), U77.6 (A)
/RS4851_B: J9.08 (Pin_8), R178.1, R238.1, U51.7 (B), U77.7 (B)
/RS4852_A: J9.09 (Pin_9), R179.2, U52.6 (A)
/RS4852_B: J9.10, R179.1, U52.7 (B)
/SPI1_MISO: J9.22, RN19.1 (R1.1), RN27.1 (R1.1), U69.10 (D4), U88.10 (D4)
/SPI1_MOSI: J9.23, RN19.4 (R4.1), RN27.4 (R4.1), U69.2 (D1), U88.2 (D1)
/SPI1_NSS: J9.25, RN19.2 (R2.1), RN27.2 (R2.1), U69.7 (D3), U88.7 (D3)
/SPI1_SCK: J9.24, RN19.3 (R3.1), RN27.3 (R3.1), U69.5 (D2), U88.5 (D2)
/SPI2_MISO: J9.27, RN18.1 (R1.1), U68.10 (D4)
/SPI2_MOSI: J9.28, RN18.4 (R4.1), U68.2 (D1)
/SPI2_NSS: J9.29, RN18.2 (R2.1), U68.7 (D3)
/SPI2_SCK: J9.30, RN18.3 (R3.1), U68.5 (D2)
/SYS_3V3: C1.1, C3.1, C33.1, C34.1, C38.1, C56.1, C74.1, C92.1, C113.2, C119.2, C132.2, C138.2, C156.2, C165.2, C170.2, C200.2, C205.2, C208.2, C230.2, L3.2, R26.1, R27.1, R44.1, R45.1, R60.1, R61.1, R62.1, R63.1, R64.1, R65.1, R68.1, R69.1, R83.1, R84.1, R96.1, R97.1, R98.1, R99.1, R100.1, R101.1, R121.2, R134.2, R154.2, R167.2, R189.1, R210.1, R211.1, R213.2, R215.1, R216.1, R222.2, R225.1, R226.1, R230.1, R231.1, R244.1, R257.1, R258.1, R260.2, R262.1, R265.2, R269.1, R273.1, TP11.1, U1.20 (VCC), U3.4 (VS), U12.1 (FB), U13.4 (VS), U17.4 (VS), U21.4 (VS), U25.4 (VS), U33.6 (IN2), U36.6 (IN2), U41.6 (IN2), U44.6 (IN2), U48.28 (VDD), U55.27 (VDDP), U55.31 (VDDI), U65.8 (IN1), U70.6 (IN2), U75.13 (A0)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
/SYS_5V: C2.1, C16.1, C28.1, C29.1, C111.2, C118.2, C130.2, C137.2, C166.2, C174.2, C206.2, C210.2, L2.2, R1.1, R2.1, R13.1, R15.1, R106.1, R107.1, R111.2, R116.1, R117.1, R128.1, R129.1, R133.2, R139.1, R140.1, R144.2, R149.1, R150.1, R161.1, R162.1, R166.2, R214.2, R227.2, R261.2, R270.2, TP10.1, U4.10 (VCC), U8.10 (VCC), U10.1 (FB), U30.6 (IN2), U36.8 (IN1), U38.6 (IN2), U44.8 (IN1), U65.6 (IN2), U71.6 (IN2), U72.2 (5V_IN), U72.4 (5V_IN), U86.6 (IN2), U90.8 (IN1)
/System_Power/POWER_IN: C6.1, C7.1, C8.1, C9.1, J1.1, R9.1, R19.2, TP4.1, U4.12 (VIN), U4.13 (VIN), U7.26 (IAP), U7.28 (ADP), U11.7 (IN1)
/System_Power/VBAT: C22.1, C23.1, J2.1, R10.1, R12.1, R21.2, TP7.1, U7.12 (BATT), U8.12 (VIN), U8.13 (VIN), U11.2 (IN2)
/UART1_RX: J9.13, RN1.1 (R1.1), RN17.1 (R1.1), RN26.1 (R1.1), U63.5 (D2), U84.5 (D2)
/UART1_TX: J9.12, RN1.2 (R2.1), RN17.2 (R2.1), RN26.2 (R2.1), U63.2 (D1), U84.2 (D1)
/UART2_RX: J9.15, RN16.1 (R1.1), U62.5 (D2)
/UART2_TX: J9.14, RN16.2 (R2.1), U62.2 (D1)
GND: C1.2, C2.2, C3.2, C4.2, C5.2, C6.2, C7.2, C8.2, C9.2, C10.2, C11.2, C14.2, C15.2, C16.2, C18.2, C19.2, C20.2, C21.2, C22.2, C23.2, C24.2, C25.2, C26.2, C28.2, C29.2, C30.2, C31.2, C33.2, C34.2, C35.2, C38.2, C39.2, C40.2, C41.2, C42.2, C43.2, C44.2, C45.2, C46.2, C47.2, C48.2, C49.2, C50.2, C51.2, C52.2, C53.2, C56.2, C57.2, C58.2, C59.2, C60.2, C61.2, C62.2, C63.2, C64.2, C65.2, C66.2, C67.2, C68.2, C69.2, C70.2, C71.2, C74.2, C75.2, C76.2, C77.2, C78.2, C79.2, C80.2, C81.2, C82.2, C83.2, C84.2, C85.2, C86.2, C87.2, C88.2, C89.2, C92.2, C93.2, C94.2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
unnamed: C12.2, R5.1
unnamed: C13.2, R6.1
unnamed: C17.1, R7.2, U7.15 (SRP), U7.16 (SRP)
unnamed: C26.1, U7.1 (VCC), U7.30 (VCC)
unnamed: C36.2, R24.1
unnamed: C37.2, R25.1
unnamed: C54.2, R42.1
unnamed: C55.2, R43.1
unnamed: C72.2, R66.1
unnamed: C73.2, R67.1
unnamed: C90.2, R81.1
unnamed: C91.2, R82.1
unnamed: C185.1, U64.71 (VCAP)
unnamed: C186.1, U64.106 (VCAP)
unnamed: C221.1, U85.71 (VCAP)
unnamed: C222.1, U85.106 (VCAP)
unnamed: D1.2 (A), R1.2
unnamed: D1.1 (K), Q1.3 (D)
unnamed: D2.2 (A), R13.2
unnamed: D2.1 (K), Q2.3 (D)
unnamed: D3.2 (A), R27.2
unnamed: D3.1 (K), Q3.3 (D)
unnamed: D4.2 (A), R45.2
unnamed: D4.1 (K), Q4.3 (D)
unnamed: D5.2 (A), R69.2
unnamed: D5.1 (K), Q5.3 (D)
unnamed: D6.2 (A), R84.2
unnamed: D6.1 (K), Q6.3 (D)
unnamed: D7.2 (A), J3.1
unnamed: D8.2 (A), R130.2
unnamed: D9.2 (A), J4.1
unnamed: D10.2 (A), R163.2
unnamed: D11.2 (A), J6.1
unnamed: D12.2 (A), R201.2
unnamed: D13.2 (A), J8.1
unnamed: D14.2 (A), R251.2
unnamed: Q1.1 (G), R2.2, U4.8 (PG), U5.3 (EN)
unnamed: Q2.1 (G), R15.2, U8.8 (PG), U9.3 (EN)
unnamed: Q3.1 (G), R26.2, U14.3 (PG)
unnamed: Q4.1 (G), R44.2, U18.3 (PG)
unnamed: Q5.1 (G), R68.2, U22.3 (PG)
unnamed: Q6.1 (G), R83.2, U26.3 (PG)
unnamed: R7.1, R8.2
unnamed: R11.1, R12.2
unnamed: R16.2, R17.1, U7.9 (NTC), U7.10 (NTC)
unnamed: R29.2, R34.1
unnamed: R33.2, R34.2, R39.1
unnamed: R46.2, R50.2
unnamed: R47.2, R52.1
unnamed: R51.2, R52.2, R57.1
unnamed: R70.2, R73.2
unnamed: R71.2, R75.1
unnamed: R74.2, R75.2, R78.1
unnamed: R85.2, R88.2
unnamed: R86.2, R90.1
unnamed: R89.2, R90.2, R93.1
unnamed: R104.2, Y1.3
unnamed: R137.2, Y2.3
unnamed: R198.2, Y3.3
unnamed: R249.2, Y4.3
unnamed: RN10.1 (R1.1), U49.1 (B2), U51.1 (R)
unnamed: RN10.2 (R2.1), U49.8 (B1Y), U51.4 (D)
unnamed: RN11.1 (R1.1), U50.1 (B2), U52.1 (R)
unnamed: RN11.2 (R2.1), U50.8 (B1Y), U52.4 (D)
unnamed: RN23.1 (R1.1), U76.1 (B2), U77.1 (R)
unnamed: RN23.2 (R2.1), U76.8 (B1Y), U77.4 (D)
unnamed: C5.1, C21.1, R4.1, U2.3 (D), U3.1 (IN+), U5.4 (CATHODE), U6.3 (D), U9.4 (CATHODE)
unnamed: U2.1 (G), U5.5 (GATE)
unnamed: C4.1, TP5.1, U2.2 (S), U4.1 (VOUT), U4.2 (VOUT), U4.3 (VOUT), U4.4 (VOUT), U4.5 (VOUT), U5.6 (ANODE)
unnamed: R3.1, U4.9 (OCP)
unnamed: C10.1, U4.7 (SR)
unnamed: C11.1, U5.1 (VCAP)
unnamed: U6.1 (G), U9.5 (GATE)
unnamed: C20.1, TP8.1, U6.2 (S), U8.1 (VOUT), U8.2 (VOUT), U8.3 (VOUT), U8.4 (VOUT), U8.5 (VOUT), U9.6 (ANODE)
unnamed: R14.2, U7.6 (ADDR)
unnamed: R5.2, U7.23 (BST1)
unnamed: R6.2, U7.17 (BST2)
unnamed: C14.1, C15.1, R8.1, R10.2, U7.18 (CFLR)
unnamed: C18.1, C19.1, R9.2, U7.22 (IN), U7.24 (IAN), U7.25 (IAN)
unnamed: C17.2, R11.2, U7.14 (SRN)
unnamed: C12.1, L1.1, U7.21 (SW1)
unnamed: C13.1, L1.2, U7.19 (SW2)
unnamed: R16.1, U7.8 (VNTC)
unnamed: R18.1, U8.9 (OCP)
unnamed: C24.1, U8.7 (SR)
unnamed: C25.1, U9.1 (VCAP)
unnamed: C27.1, U10.6 (BST)
unnamed: C30.1, C35.1, TP9.1, U10.2 (EN), U10.3 (IN), U11.1 (OUT), U11.8 (OUT), U12.2 (EN), U12.3 (IN)
unnamed: C27.2, L2.1, U10.5 (SW)
unnamed: R23.2, U11.10 (ILIM)
unnamed: R19.1, R20.2, U11.5 (OV1)
unnamed: R21.1, R22.2, U11.4 (OV2)
unnamed: C31.1, U11.11 (SS)
unnamed: C32.1, U12.6 (BST)
unnamed: C32.2, L3.1, U12.5 (SW)
unnamed: R31.1, U13.1 (IN+), U14.6 (OUT)
unnamed: R30.2, R35.1, U14.1 (EN/UVLO), U14.4 (PGTH)
unnamed: C43.1, C44.1, C45.1, C46.1, C47.1, C48.1, C52.1, R29.1, R30.1, TP13.1, U14.5 (IN), U16.12 (VOUT)
unnamed: R35.2, R38.1, U14.2 (OVLO)
unnamed: R28.2, R32.2, U15.1 (EN/UVLO), U15.4 (PGTH)
unnamed: R41.1, U15.9 (ILM)
unnamed: C51.1, U15.10 (ITIMER)
unnamed: C39.1, C40.1, C41.1, TP12.1, U15.6 (OUT), U16.1 (VIN)
unnamed: R36.2, R37.1, U15.2 (OVLO)
unnamed: C50.1, U15.7 (dVdt)
unnamed: R24.2, U16.16 (BST1)
unnamed: R25.2, U16.13 (BST2)
unnamed: R33.1, U16.8 (FB)
unnamed: C42.1, R40.1, U16.7 (OC)
unnamed: C36.1, L4.1, U16.15 (SW1)
unnamed: C37.1, L4.2, U16.14 (SW2)
unnamed: C53.1, U16.9 (VCC)
unnamed: R49.2, U17.1 (IN+), U18.6 (OUT)
unnamed: R48.2, R53.1, U18.1 (EN/UVLO), U18.4 (PGTH)
unnamed: C61.1, C62.1, C63.1, C64.1, C65.1, C66.1, C70.1, R47.1, R48.1, TP16.1, U18.5 (IN), U20.12 (VOUT)
unnamed: R53.2, R56.1, U18.2 (OVLO)
unnamed: U19.1 (EN/UVLO), U19.4 (PGTH)
unnamed: R59.1, U19.9 (ILM)
unnamed: C69.1, U19.10 (ITIMER)
unnamed: C57.1, C58.1, C59.1, TP15.1, U19.6 (OUT), U20.1 (VIN)
unnamed: R54.2, R55.1, U19.2 (OVLO)
unnamed: C68.1, U19.7 (dVdt)
unnamed: R42.2, U20.16 (BST1)
unnamed: R43.2, U20.13 (BST2)
unnamed: R51.1, U20.8 (FB)
unnamed: C60.1, R58.1, U20.7 (OC)
unnamed: C54.1, L5.1, U20.15 (SW1)
unnamed: C55.1, L5.2, U20.14 (SW2)
unnamed: C71.1, U20.9 (VCC)
unnamed: R72.2, U21.1 (IN+), U22.6 (OUT)
unnamed: C79.1, C80.1, C81.1, C82.1, C83.1, C84.1, C88.1, R71.1, TP19.1, U22.5 (IN), U24.12 (VOUT)
unnamed: U23.1 (EN/UVLO), U23.4 (PGTH)
unnamed: R80.1, U23.9 (ILM)
unnamed: C87.1, U23.10 (ITIMER)
unnamed: C75.1, C76.1, C77.1, TP18.1, U23.6 (OUT), U24.1 (VIN)
unnamed: R76.2, R77.1, U23.2 (OVLO)
unnamed: C86.1, U23.7 (dVdt)
unnamed: R66.2, U24.16 (BST1)
unnamed: R67.2, U24.13 (BST2)
unnamed: R74.1, U24.8 (FB)
unnamed: C78.1, R79.1, U24.7 (OC)
unnamed: C72.1, L6.1, U24.15 (SW1)
unnamed: C73.1, L6.2, U24.14 (SW2)
unnamed: C89.1, U24.9 (VCC)
unnamed: R87.2, U25.1 (IN+), U26.6 (OUT)
unnamed: C97.1, C98.1, C99.1, C100.1, C101.1, C102.1, C106.1, R86.1, TP22.1, U26.5 (IN), U28.12 (VOUT)
unnamed: U27.1 (EN/UVLO), U27.4 (PGTH)
unnamed: R95.1, U27.9 (ILM)
unnamed: C105.1, U27.10 (ITIMER)
unnamed: C93.1, C94.1, C95.1, TP21.1, U27.6 (OUT), U28.1 (VIN)
unnamed: R91.2, R92.1, U27.2 (OVLO)
unnamed: C104.1, U27.7 (dVdt)
unnamed: R81.2, U28.16 (BST1)
unnamed: R82.2, U28.13 (BST2)
unnamed: R89.1, U28.8 (FB)
unnamed: C96.1, R94.1, U28.7 (OC)
unnamed: C90.1, L7.1, U28.15 (SW1)
unnamed: C91.1, L7.2, U28.14 (SW2)
unnamed: C107.1, U28.9 (VCC)
unnamed: R112.1, U30.4 (ILIM)
unnamed: R109.2, U31.42 (PA9)
unnamed: R110.2, U31.43 (PA10)
unnamed: U31.5 (PH0), Y1.1
unnamed: R104.1, U31.6 (PH1)
unnamed: C116.1, U31.30 (VCAP_1)
unnamed: R122.1, U32.16 (S1A)
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
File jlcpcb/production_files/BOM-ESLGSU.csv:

Comment,Designator,Footprint,LCSC
TXB0104RUT,"U66,U67,U87",T-UQFN-12,C105266
FXMA2102L8X,"U34,U42,U58,U59,U82",UQFN8_MICROPAK,C107408
STM32H743ZITx,"U64,U85",LQFP-144_20x20mm_P0.5mm,C114408
1K,"R41,R59,R80,R95",R_0402_1005Metric,C11702
2.2u,"C116,C135,C185,C186,C221,C222",C_0402_1005Metric,C12530
10118194-0001LF,"J5,J7",AMPHENOL_10118194-0001LF,C132563
100u,"C40,C58,C76,C9,C94",CP_Elec_6.3x7.7,C134220
TPS2115ADRBR,"U30,U33,U36,U38,U41,U44,U65,U70,U71,U86,U89,U90",VSON-8-1EP_3x3mm_P0.65mm_EP1.65x2.4mm,C140321
1n,"C10,C24",C_0402_1005Metric,C1523
220p,"C104,C50,C68,C86",C_0402_1005Metric,C1530
2.2n,"C105,C51,C69,C87",C_0402_1005Metric,C1531
22n,"C20,C4,C42,C60,C78,C96",C_0402_1005Metric,C1532
100p,"C115,C134,C159,C160,C202",C_0402_1005Metric,C1546
10u,"C18,C19,C30,C35,C6,C7,C8",C_0805_2012Metric,C15850
0R,"R24,R25,R42,R43,R5,R6,R66,R67,R81,R82",R_0402_1005Metric,C17168
TXU0202DTTR,"U49,U50,U60,U61,U76,U83",SOT833-1-XSON8,C18197534
TCAN1051GVDRBRQ,"U29,U37,U45,U46,U73",DFN-8-1EP_3x3mm_P0.65mm_EP1.55x2.4mm,C1848110
THVD1450DRBR,"U51,U52,U77",DFN-8-1EP_3x3mm_P0.65mm_EP1.55x2.4mm,C1850226
1N5819,"D11,D13,D7,D9",D_SOD-323,C191023
ESD7004MUTAG,"U54,U80",UDFN10_ESD,C1972960
SRP1038A-4R7M,"L1,L4,L5,L6,L7",L_Vishay_IHLP-4040,C2041319
AP63205WU-7,U10,TSOT-23-6,C2071056
TZ-P2-0603GTCS1-0.6T,"D1,D10,D12,D14,D2,D3,D4,D5,D6,D8",LED_0603_1608Metric,C2286
4.7u,"C120,C139,C178,C214,C26",C_0402_1005Metric,C23733
1R,"R11,R276,R278,R7",R_0402_1005Metric,C25086
200R,"R1,R13",R_0402_1005Metric,C25087
33R,"R130,R163,R201,R251,R27,R45,R69,R84",R_0402_1005Metric,C25105
510R,"R112,R124,R132,R145,R157,R165,R212,R223,R228,R259,R266,R271",R_0402_1005Metric,C25123
100K,"R105,R114,R127,R138,R147,R160,R170,R171,R172,R182,R184,R19,R202,R203,R21,R217,R218,R233,R234,R240,R252,R263,R47",R_0402_1005Metric,C25741
10K,"R119,R120,R122,R123,R14,R15,R152,R153,R155,R156,R16,R17,R176,R177,R190,R191,R192,R193,R194,R195,R196,R197,R2,R230,R231,R237,R245,R246,R247,R248,R267,R268",R_0402_1005Metric,C25744
12K,R38,R_0402_1005Metric,C25752
150K,"R39,R71,R86",R_0402_1005Metric,C25755
15K,"R29,R37,R55,R56,R77,R92",R_0402_1005Metric,C25756
200K,"R102,R106,R107,R108,R115,R116,R117,R118,R126,R128,R129,R131,R135,R139,R140,R141,R148,R149,R150,R151,R159,R161,R162,R164,R173,R174,R175,R180,R181,R183,R185,R186,R187,R188,R189,R199,R200,R205,R206,R208,R209,R210,R211,R215,R216,R219,R220,R221,R225,R226,R235,R236,R239,R241,R242,R243,R244,R250,R254,R256,R257,R258,R262,R264,R269,R272,R273,R274,R28,R33,R46,R51,R52,R70,R74,R85,R89",R_0402_1005Metric,C25764
20K,"R18,R3",R_0402_1005Metric,C25765
220K,"R75,R90",R_0402_1005Metric,C25767
22K,"R30,R40,R58,R79,R94",R_0402_1005Metric,C25768
27K,"R23,R36,R54,R76,R91",R_0402_1005Metric,C25771
330K,R34,R_0402_1005Metric,C25778
47K,"R26,R44,R68,R83",R_0402_1005Metric,C25792
51K,"R48,R78,R93",R_0402_1005Metric,C25794
75K,R57,R_0402_1005Metric,C25798
1.5K,R35,R_0402_1005Metric,C25867
2.2K,R53,R_0402_1005Metric,C25879
49.9K,"R285,R286,R287,R288",R_0402_1005Metric,C25897
4.7K,"R100,R101,R60,R61,R62,R63,R64,R65,R96,R97,R98,R99",R_0402_1005Metric,C25900
5.6K,"R20,R22",R_0402_1005Metric,C25908
8.2K,"R32,R50,R73,R88",R_0402_1005Metric,C25924
TMUX1574RSVR,"U32,U35,U40,U43,U47,U53,U56,U57,U62,U63,U68,U69,U74,U78,U81,U84,U88",T-UQFN-16,C2673120
TCA9544APWR,U1,TSSOP-20_4.4x6.5mm_P0.65mm,C2674619
FH-00339,U72,PI_ZERO_2_W,C2685112
Conn_01x06_Pin,"J3,J4,J6,J8",PinHeader_1x06_P1.27mm_Vertical_SMD_Pin1Right,C2881612
AMPHENOL_62684-401100ALF,J9,AMPHENOL_62684-401100ALF,C2904111
CY8C9520A,"U48,U75,U91",SSOP-28_5.3x10.2mm_P0.65mm,C2953731
100n,"C1,C102,C108,C109,C11,C110,C111,C112,C113,C114,C117,C118,C119,C12,C122,C123,C124,C125,C126,C127,C128,C129,C13,C130,C131,C132,C133,C136,C137,C138,C141,C142,C143,C144,C145,C146,C147,C148,C149,C150,C151,C152,C153,C154,C155,C156,C157,C158,C161,C162,C163,C164,C165,C166,C167,C168,C169,C17,C170,C171,C172,C173,C174,C176,C177,C180,C181,C182,C183,C184,C187,C188,C189,C190,C191,C192,C193,C194,C195,C196,C197,C198,C199,C200,C201,C203,C204,C205,C206,C207,C208,C209,C21,C210,C212,C213,C216,C217,C218,C219,C220,C223,C224,C225,C226,C227,C228,C229,C230,C233,C234,C235,C236,C237,C25,C27,C3,C31,C32,C36,C37,C38,C39,C48,C5,C54,C55,C56,C57,C66,C72,C73,C74,C75,C84,C90,C91,C92,C93",C_0402_1005Metric,C307331
SPM5020T-4R7M-LR,"L2,L3",L_Vishay_IHLP-2020,C307807
LM73100RPWR,"U14,U18,U22,U26",VQFN-HR,C3210761
CSTNE8M00G55A,"Y3,Y4",Resonator_SMD_Murata_CSTxExxV-3Pin_3.0x1.1mm,C341523
TPS259474LRPWR,"U15,U19,U23,U27",VQFN-HR,C3662807
TPS2553DRVR,"U94,U95,U96,U97",WSON-6-1EP_2x2mm_P0.65mm_EP1x1.6mm,C411878
22u,"C100,C101,C14,C15,C22,C23,C28,C29,C33,C34,C41,C43,C44,C45,C46,C47,C59,C61,C62,C63,C64,C65,C77,C79,C80,C81,C82,C83,C95,C97,C98,C99",C_0805_2012Metric,C45783
5m,"R10,R31,R4,R49,R72,R87,R9",R_1206_3216Metric,C464975
VBQF1303,"U2,U6",V-DFN3030-8,C481054
TPS2121RUXR,U11,Texas_VQFN-HR-12_2x2.5mm_P0.5mm,C485916
RE1C002UNTCL,"Q1,Q2,Q3,Q4,Q5,Q6",SOT-416,C509959
1u,"C103,C106,C107,C121,C140,C16,C175,C179,C2,C211,C215,C231,C232,C49,C52,C53,C67,C70,C71,C85,C88,C89",C_0402_1005Metric,C52923
AP74700QW6-7,"U5,U9",SOT-23-6,C5381661
MP2651GVT,U7,TQFN30_MP2651,C5632167
AP63203WU-7,U12,TSOT-23-6,C780769
INA219AIDCNR,"U13,U17,U21,U25,U3",SOT-23-8,C87469
NCP45770IMN24TWG,"U4,U8",WDFN-12-1EP_3x3mm_P0.45mm_EP1.7x2.5mm,C892480
STM32F412RETx,"U31,U39",LQFP-64_10x10mm_P0.5mm,C89374
MP28167-A,U16,QFN-16-MP28167,
MP28167-A,U28,QFN-16-MP28167,
MP28167-A,U24,QFN-16-MP28167,
1054301108,J10,MOLEX_1054301108,
MP28167-A,U20,QFN-16-MP28167,
